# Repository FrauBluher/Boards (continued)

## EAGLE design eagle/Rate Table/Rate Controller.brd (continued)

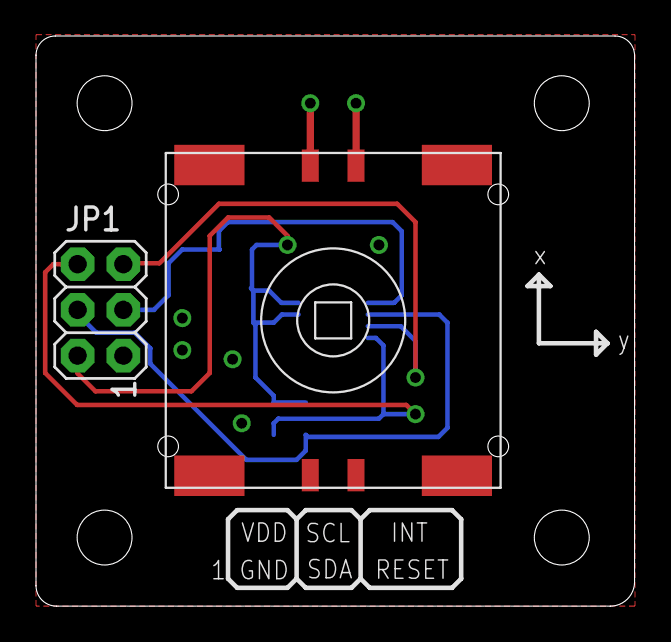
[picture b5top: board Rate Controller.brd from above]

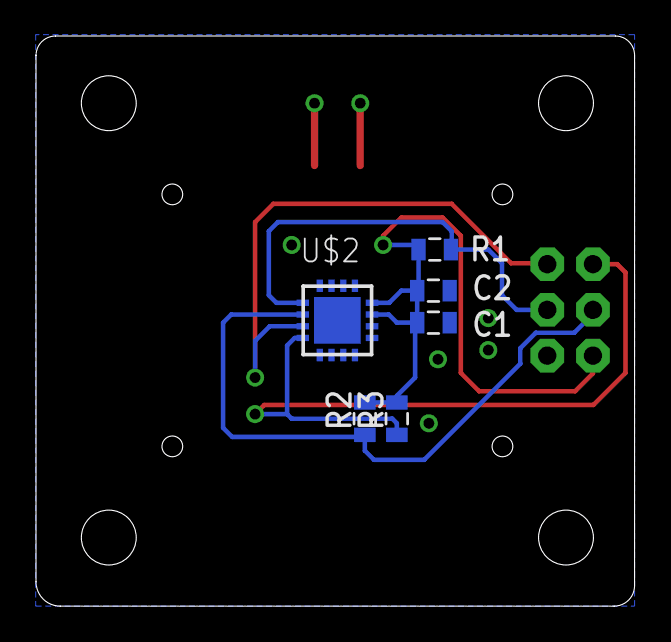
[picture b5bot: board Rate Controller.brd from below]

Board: 2 copper layers, 33.3 x 31.7 mm, 12 parts (6 on the bottom side), 6 nets.

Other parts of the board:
E$1, E$2, E$3, E$4: STAND-OFF-TIGHT

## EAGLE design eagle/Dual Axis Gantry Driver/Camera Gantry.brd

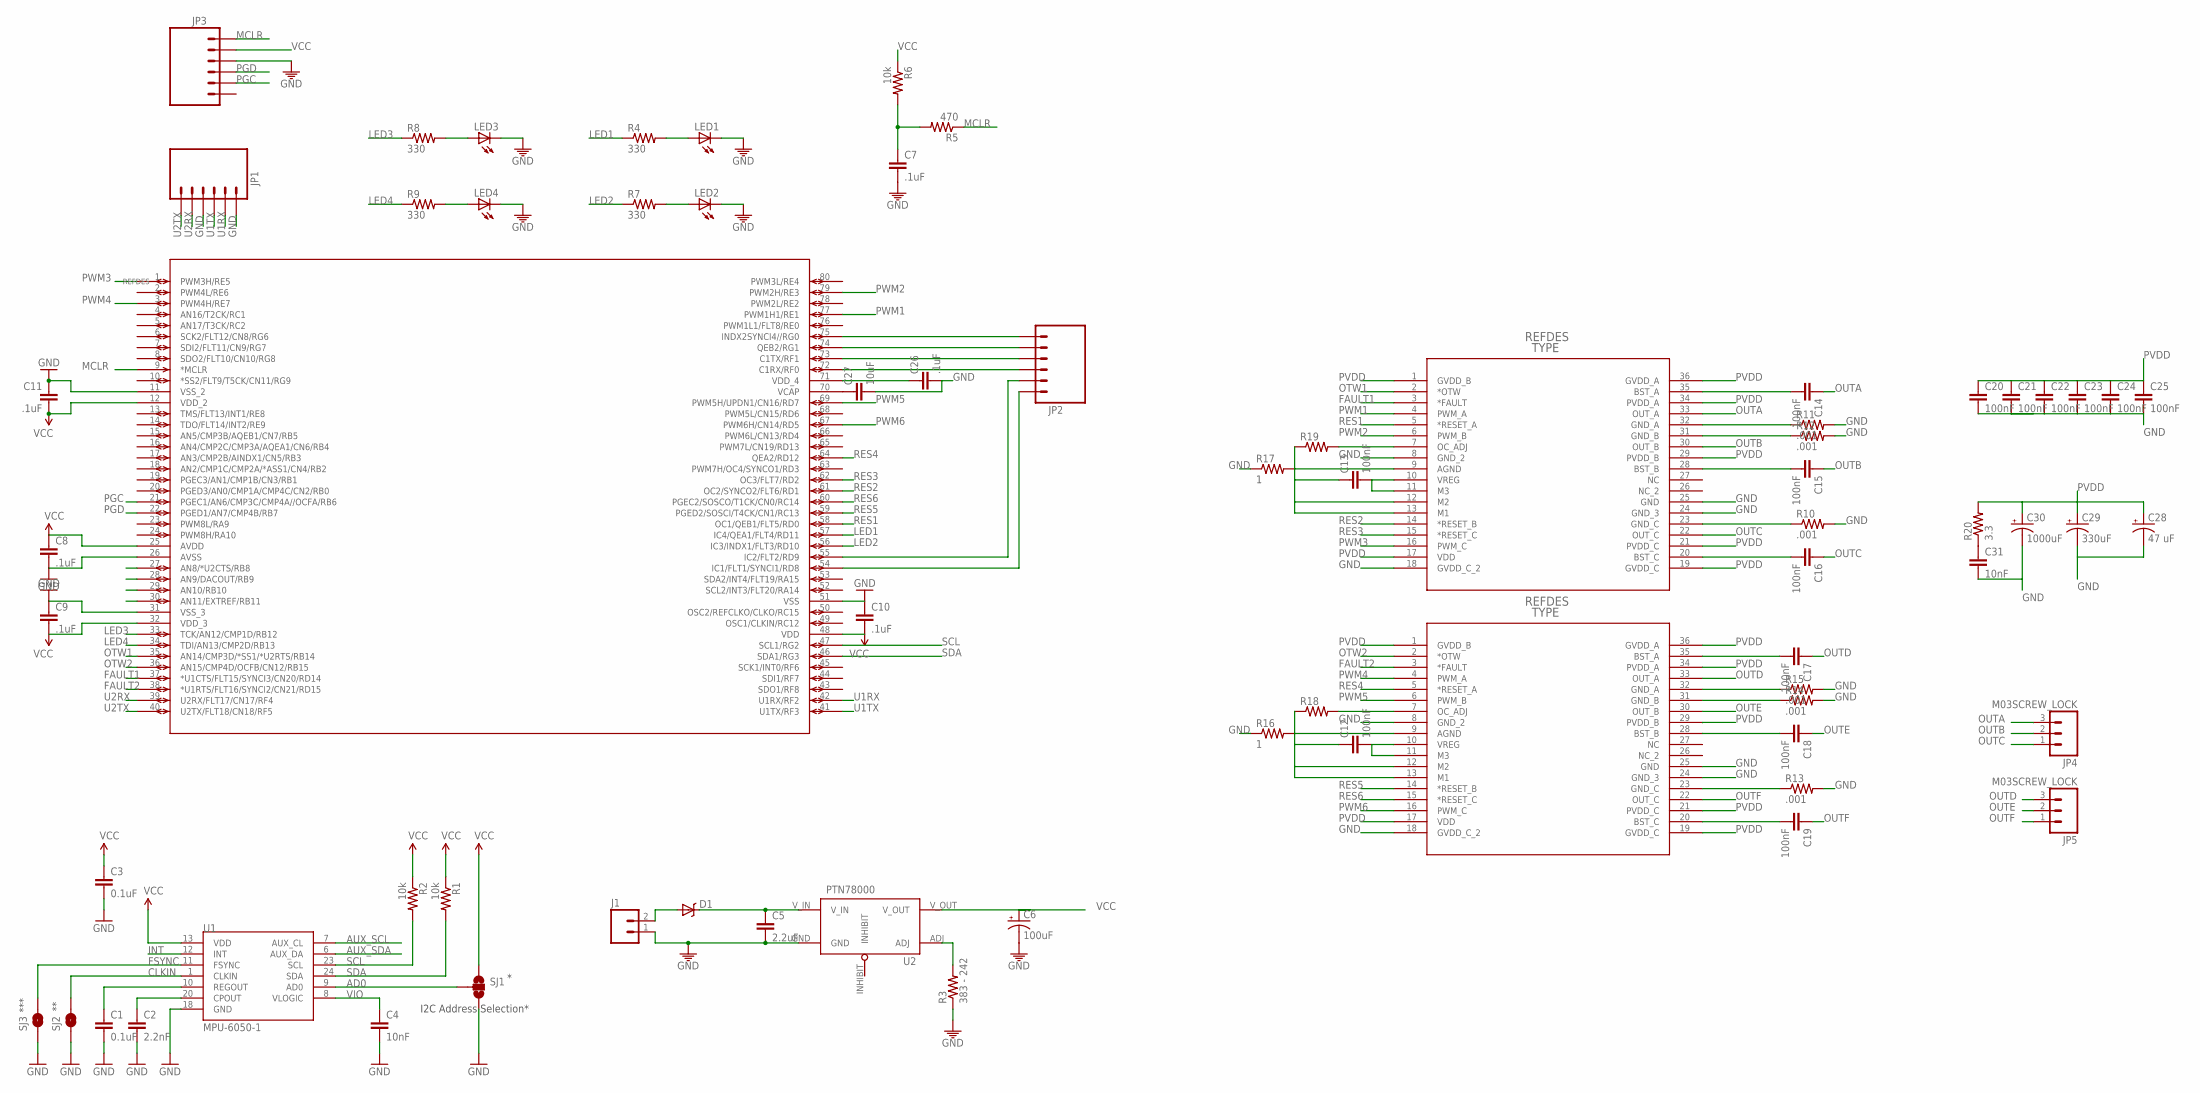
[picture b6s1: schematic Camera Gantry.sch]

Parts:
C1, C3: 0.1uF; 1206
C2: 2.2nF; 1206
C4, C31: 10nF; 1206
C5: 2.2uF; 1206
C6: 100uF; CPOL-RADIAL-100UF-25V
C7, C8, C9, C10, C11, C26: .1uF; 1206
C12, C13, C14, C15, C16, C17, C18, C19, C20, C21, C22, C23, C24, C25: 100nF; 1206
C27: 10uF; 1206
C28: 47 uF; CPOL-RADIAL-10UF-25V
C29: 330uF; CPOL-RADIAL-100UF-25V
C30: 1000uF; CPOL-RADIAL-1000UF-25V
D1: DIODE-SCHOTTKY240A; SMA-DIODE-B240A
J1: M025MM; SCREWTERMINAL-5MM-2
JP1, JP2: M06SIP; 1X06
JP3: M06LOCK; 1X06_LOCK
JP4, JP5: M03SCREW_LOCK; SCREWTERMINAL-3.5MM-3_LOCK.007S
LED1, LED2, LED3, LED4: LED1206; LED-1206
R1, R2, R6: 10k; 0805
R3: 383 - 242; 0805
R4, R7, R8, R9: 330; 0805
R5: 470; 0805
R10, R11, R12, R13, R14, R15: .001; R2512
R16, R17: 1; 0805
R18, R19: RESISTOR0805-RES; 0805
R20: 3.3; 0805
SJ1: SOLDERJUMPER_2WAYPASTE2&3; SJ_3_PASTE2&3
SJ2, SJ3: SOLDERJUMPERTRACE; SJ_2S-TRACE
U1: MPU-6050-1; QFN-24-4MM2
U2: PTN78000
U3, U4: DRV8332_DKD_36; DKD36
U$1: DSPIC33FJ64GS608; TQFP80_12X12MC

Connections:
AD0: SJ1.2, U1.9 (AD0)
AUX_SCL: U1.7 (AUX_CL)
AUX_SDA: U1.6 (AUX_DA)
CLKIN: SJ2.2, U1.1 (CLKIN)
FAULT1: U3.3 (*FAULT), U$1.37 (*U1CTS/FLT15/SYNCI3/CN20/RD14)
FAULT2: U4.3 (*FAULT), U$1.38 (*U1RTS/FLT16/SYNCI2/CN21/RD15)
FSYNC: SJ3.2, U1.11 (FSYNC)
GND: C1.2, C2.2, C3.2, C4.2, C5.2, C6.2 (-), C7.2, C8.2, C9.1, C10.1, C11.1, C20.2, C21.2, C22.2, C23.2, C24.2, C25.2, C26.2, C27.2, C28.2 (-), C29.2 (-), C30.2 (-), C31.2, J1.1, JP1.1, JP1.4, JP3.3, LED1.C, LED2.C, LED3.C, LED4.C, R3.1, R10.2, R11.2, R12.2, R13.2, R14.2, R15.2, R16.1, R17.1, SJ1.3, SJ2.1, SJ3.1, U1.18 (GND), U2.GND, U3.8 (GND_2), U3.18 (GVDD_C_2), U3.24 (GND_3), U3.25 (GND), U4.8 (GND_2), U4.18 (GVDD_C_2), U4.24 (GND_3), U4.25 (GND), U$1.11 (VSS_2), U$1.26 (AVSS), U$1.31 (VSS_3), U$1.51 (VSS)
INT: U1.12 (INT)
LED1: R4.1, U$1.57 (IC4/QEA1/FLT4/RD11)
LED2: R7.1, U$1.56 (IC3/INDX1/FLT3/RD10)
LED3: R8.1, U$1.33 (TCK/AN12/CMP1D/RB12)
LED4: R9.1, U$1.34 (TDI/AN13/CMP2D/RB13)
MCLR: JP3.1, R5.1, U$1.9 (*MCLR)
unnamed: LED1.A, R4.2
unnamed: C7.1, R5.2, R6.2
unnamed: C2.1, U1.20 (CPOUT)
unnamed: LED2.A, R7.2
unnamed: C1.1, U1.10 (REGOUT)
unnamed: R3.2, U2.ADJ
unnamed: D1.A, J1.2
unnamed: LED3.A, R8.2
unnamed: LED4.A, R9.2
unnamed: R11.1, U3.32 (GND_A)
unnamed: R12.1, U3.31 (GND_B)
unnamed: R10.1, U3.23 (GND_C)
unnamed: C13.1, R17.2, R19.1, U3.9 (AGND), U3.12 (M2), U3.13 (M1)
unnamed: C12.1, R16.2, R18.1, U4.9 (AGND), U4.12 (M2), U4.13 (M1)
unnamed: R18.2, U4.7 (OC_ADJ)
unnamed: C12.2, U4.10 (VREG), U4.11 (M3)
unnamed: C13.2, U3.10 (VREG), U3.11 (M3)
unnamed: R15.1, U4.32 (GND_A)
unnamed: R14.1, U4.31 (GND_B)
unnamed: R13.1, U4.23 (GND_C)
unnamed: C17.2, U4.35 (BST_A)
unnamed: C18.2, U4.28 (BST_B)
unnamed: C19.2, U4.20 (BST_C)
unnamed: C14.2, U3.35 (BST_A)
unnamed: C15.2, U3.28 (BST_B)
unnamed: C16.2, U3.20 (BST_C)
unnamed: JP2.3, U$1.72 (C1RX/RF0)
unnamed: JP2.4, U$1.73 (C1TX/RF1)
unnamed: JP2.5, U$1.74 (QEB2/RG1)
unnamed: R19.2, U3.7 (OC_ADJ)
unnamed: JP2.6, U$1.75 (INDX2SYNCI4//RG0)
unnamed: JP2.1, U$1.54 (IC1/FLT1/SYNCI1/RD8)
unnamed: JP2.2, U$1.55 (IC2/FLT2/RD9)
unnamed: C26.1, U$1.71 (VDD_4)
unnamed: C27.1, U$1.70 (VCAP)
unnamed: C31.1, R20.1
OTW1: U3.2 (*OTW), U$1.35 (AN14/CMP3D/*SS1/*U2RTS/RB14)
OTW2: U4.2 (*OTW), U$1.36 (AN15/CMP4D/OCFB/CN12/RB15)
OUTA: C14.1, JP4.3, U3.33 (OUT_A)
OUTB: C15.1, JP4.2, U3.30 (OUT_B)
OUTC: C16.1, JP4.1, U3.22 (OUT_C)
OUTD: C17.1, JP5.3, U4.33 (OUT_A)
OUTE: C18.1, JP5.2, U4.30 (OUT_B)
OUTF: C19.1, JP5.1, U4.22 (OUT_C)
PGC: JP3.5, U$1.21 (PGEC1/AN6/CMP3C/CMP4A//OCFA/RB6)
PGD: JP3.4, U$1.22 (PGED1/AN7/CMP4B/RB7)
PVDD: C5.1, C20.1, C21.1, C22.1, C23.1, C24.1, C25.1, C28.1 (+), C29.1 (+), C30.1 (+), D1.C, R20.2, U2.V_IN, U3.1 (GVDD_B), U3.17 (VDD), U3.19 (GVDD_C), U3.21 (PVDD_C), U3.29 (PVDD_B), U3.34 (PVDD_A), U3.36 (GVDD_A), U4.1 (GVDD_B), U4.17 (VDD), U4.19 (GVDD_C), U4.21 (PVDD_C), U4.29 (PVDD_B), U4.34 (PVDD_A), U4.36 (GVDD_A)
PWM1: U3.4 (PWM_A), U$1.77 (PWM1H1/RE1)
PWM2: U3.6 (PWM_B), U$1.79 (PWM2H/RE3)
PWM3: U3.16 (PWM_C), U$1.1 (PWM3H/RE5)
PWM4: U4.4 (PWM_A), U$1.3 (PWM4H/RE7)
PWM5: U4.6 (PWM_B), U$1.69 (PWM5H/UPDN1/CN16/RD7)
PWM6: U4.16 (PWM_C), U$1.67 (PWM6H/CN14/RD5)
RES1: U3.5 (*RESET_A), U$1.58 (OC1/QEB1/FLT5/RD0)
RES2: U3.14 (*RESET_B), U$1.61 (OC2/SYNCO2/FLT6/RD1)
RES3: U3.15 (*RESET_C), U$1.62 (OC3/FLT7/RD2)
RES4: U4.5 (*RESET_A), U$1.64 (QEA2/RD12)
RES5: U4.14 (*RESET_B), U$1.59 (PGED2/SOSCI/T4CK/CN1/RC13)
RES6: U4.15 (*RESET_C), U$1.60 (PGEC2/SOSCO/T1CK/CN0/RC14)
SCL: R2.2, U1.23 (SCL), U$1.47 (SCL1/RG2)
SDA: R1.2, U1.24 (SDA), U$1.46 (SDA1/RG3)
U1RX: JP1.2, U$1.42 (U1RX/RF2)
U1TX: JP1.3, U$1.41 (U1TX/RF3)
U2RX: JP1.5, U$1.39 (U2RX/FLT17/CN17/RF4)
U2TX: JP1.6, U$1.40 (U2TX/FLT18/CN18/RF5)
VCC: C3.1, C6.1 (+), C8.1, C9.2, C10.2, C11.2, JP3.2, R1.1, R2.1, R6.1, SJ1.1, U1.13 (VDD), U2.V_OUT, U$1.12 (VDD_2), U$1.25 (AVDD), U$1.32 (VDD_3), U$1.48 (VDD)
VIO: C4.1, U1.8 (VLOGIC)

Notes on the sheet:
I2C Address Selection*
***

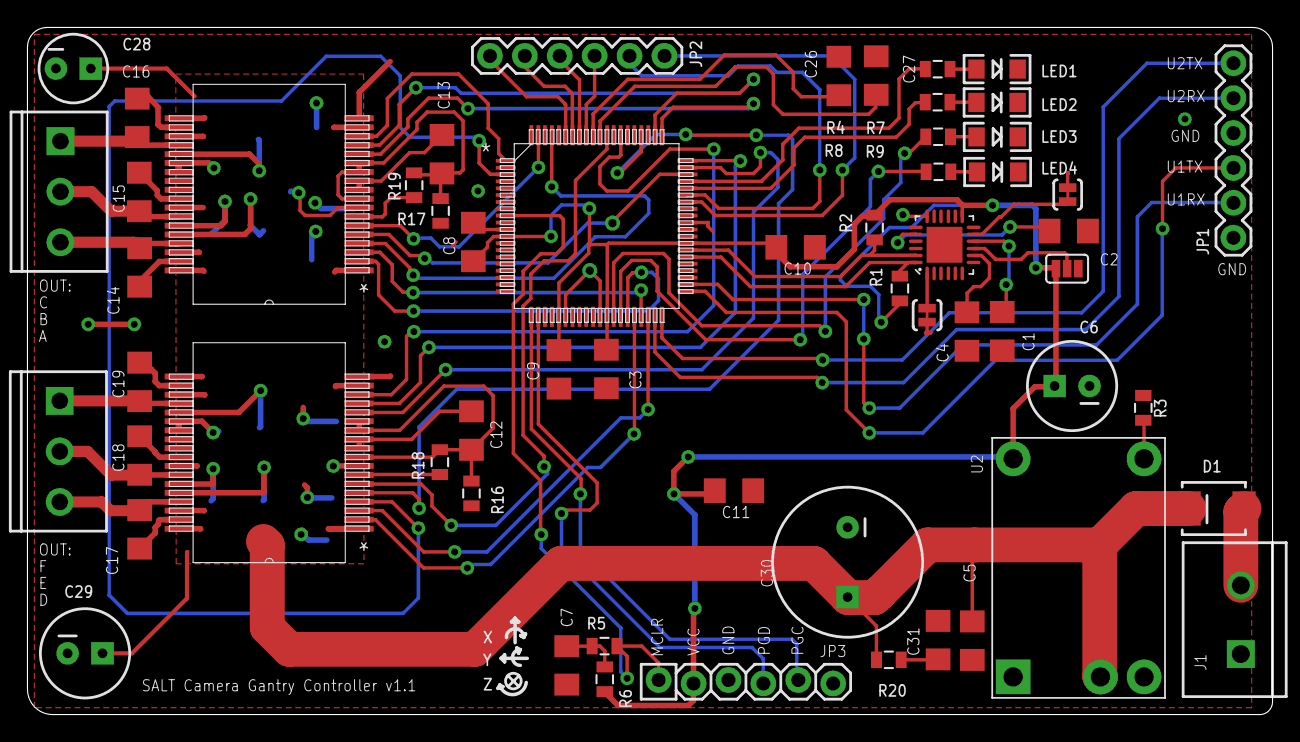
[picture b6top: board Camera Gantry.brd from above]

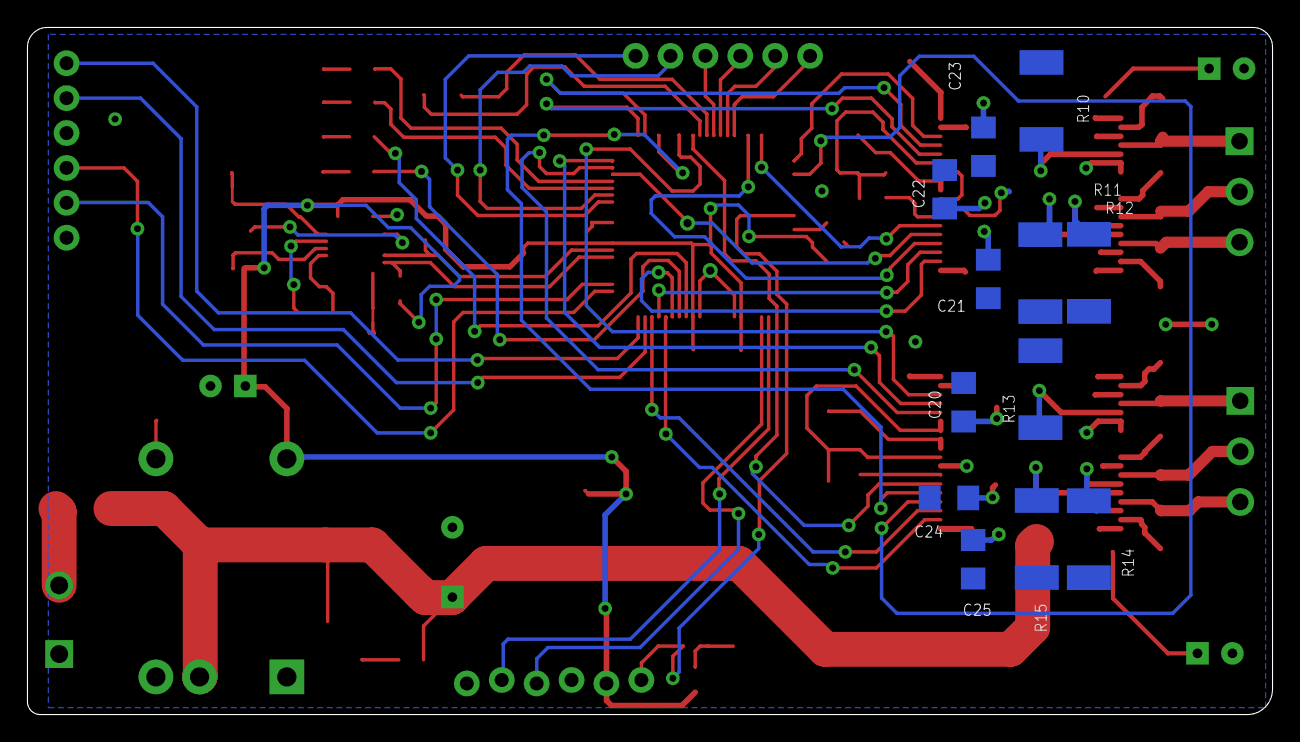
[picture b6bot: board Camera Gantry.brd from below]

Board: 2 copper layers, 90.6 x 50.0 mm, 70 parts (12 on the bottom side), 78 nets.

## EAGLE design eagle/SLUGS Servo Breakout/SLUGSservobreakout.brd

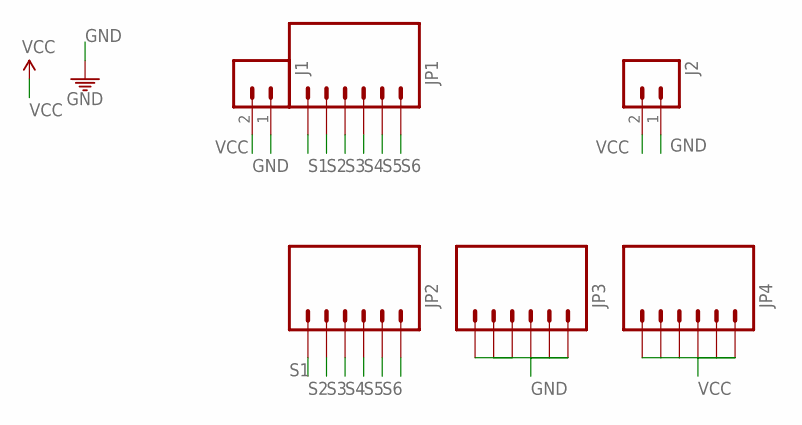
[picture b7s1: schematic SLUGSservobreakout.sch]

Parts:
J1, J2: M02PTH; 1X02
JP1, JP2, JP3, JP4: M06SIP; 1X06

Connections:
GND: J1.1 (2), J2.1 (2), JP3.1, JP3.2, JP3.3, JP3.4, JP3.5, JP3.6
S1: JP1.6, JP2.6
S2: JP1.5, JP2.5
S3: JP1.4, JP2.4
S4: JP1.3, JP2.3
S5: JP1.2, JP2.2
S6: JP1.1, JP2.1
VCC: J1.2 (1), J2.2 (1), JP4.1, JP4.2, JP4.3, JP4.4, JP4.5, JP4.6

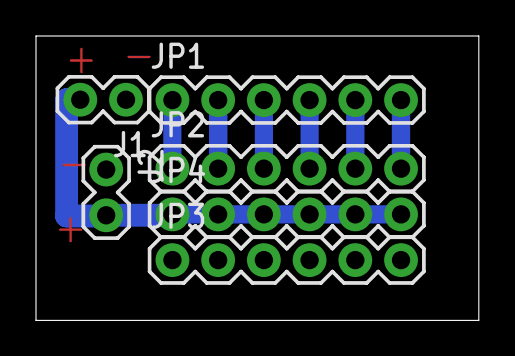
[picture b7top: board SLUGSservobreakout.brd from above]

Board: 2 copper layers, 24.6 x 15.8 mm, 6 parts (0 on the bottom side), 8 nets.

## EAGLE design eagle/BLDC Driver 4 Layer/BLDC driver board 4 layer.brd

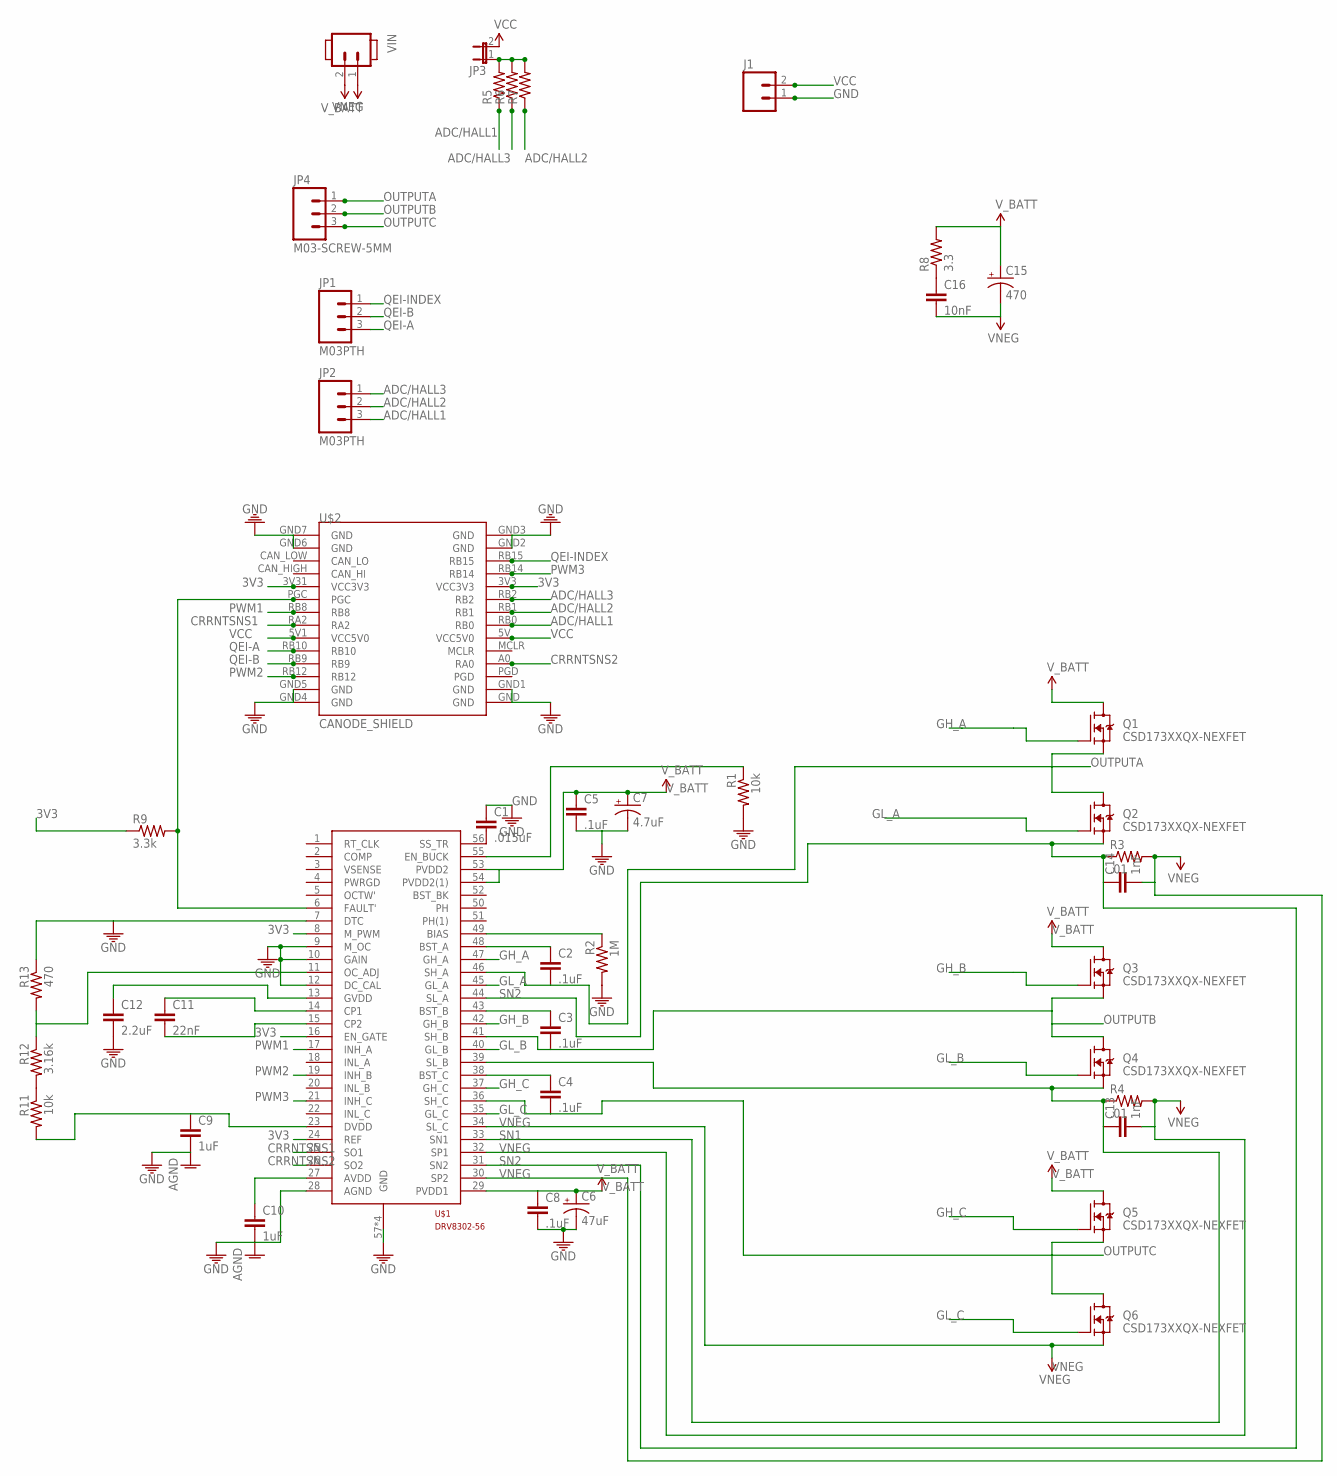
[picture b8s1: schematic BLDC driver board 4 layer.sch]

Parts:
C1: .015uF; 1206
C2, C3, C4, C5, C8: .1uF; 1206
C6: 47uF; CPOL-RADIAL-6.3MM
C7: 4.7uF; CPOL-RADIA-5MM
C9, C10: 1uF; 1206
C11: 22nF; 1206
C12: 2.2uF; 1206
C13, C14: 1nF; 1206
C15: 470; CPOL-RADIAL-1000UF-63V
C16: 10nF; 1206
J1: M02; SOCKET-MALE-2.54MM-2
JP1, JP2: M03PTH; 1X03
JP3: JP1E; JP1
JP4: M03-SCREW-5MM; SCREWTERMINAL-5MM-3
Q1, Q2, Q3, Q4, Q5, Q6: CSD173XXQX-NEXFET; CSD173XXQX
R1, R11: 10k; 0805
R2: 1M; 0805
R3, R4: .01; SMT-REF
R5, R6, R7: RESISTOR0805-RES; 0805
R8: 3.3; 1206
R9: 3.3k; 0805
R12: 3.16k; 0805
R13: 470; 0805
U$1: DRV8302-56; HTSSOP56
U$2: CANODE_SHIELD
VIN: SCREWTERM02; SCREW_TERMINAL-5.08MM-2

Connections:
3V3: R9.1, U$1.8 (M_PWM), U$1.16 (EN_GATE), U$1.24 (REF), U$2.3V3 (VCC3V3), U$2.3V31 (VCC3V3)
ADC/HALL1: JP2.3, R6.1, U$2.RB0
ADC/HALL2: JP2.2, R7.1, U$2.RB1
ADC/HALL3: JP2.1, R5.1, U$2.RB2
CRRNTSNS1: U$1.25 (SO1), U$2.RA2
CRRNTSNS2: U$1.26 (SO2), U$2.A0 (RA0)
GH_A: Q1.G, U$1.47 (GH_A)
GH_B: Q3.G, U$1.42 (GH_B)
GH_C: Q5.G, U$1.37 (GH_C)
GL_A: Q2.G, U$1.45 (GL_A)
GL_B: Q4.G, U$1.40 (GL_B)
GL_C: Q6.G, U$1.35 (GL_C)
GND: C1.1, C5.2, C6.2 (-), C7.2 (-), C8.2, C9.2, C10.2, C12.2, J1.1, R1.2, R2.2, R13.1, U$1.7 (DTC), U$1.9 (M_OC), U$1.10 (GAIN), U$1.12 (DC_CAL), U$1.28 (AGND), U$1.57 (GND), U$1.P$1 (GND), U$1.P$2 (GND), U$1.P$3 (GND), U$2.GND, U$2.GND1 (GND), U$2.GND2 (GND), U$2.GND3 (GND), U$2.GND4 (GND), U$2.GND5 (GND), U$2.GND6 (GND), U$2.GND7 (GND)
unnamed: C1.2, U$1.56 (SS_TR)
unnamed: R9.2, U$1.6 (FAULT'), U$2.PGC
unnamed: R2.1, U$1.49 (BIAS)
unnamed: C2.1, U$1.48 (BST_A)
unnamed: C3.1, U$1.43 (BST_B)
unnamed: C16.1, R8.1
unnamed: C4.1, U$1.38 (BST_C)
unnamed: R11.1, R12.2
unnamed: R1.1, U$1.55 (EN_BUCK)
unnamed: R12.1, R13.2, U$1.11 (OC_ADJ)
unnamed: JP3.1, R5.2, R6.2, R7.2
unnamed: C10.1, U$1.27 (AVDD)
unnamed: C9.1, R11.2, U$1.23 (DVDD)
unnamed: C11.1, U$1.14 (CP1)
unnamed: C11.2, U$1.15 (CP2)
unnamed: C12.1, U$1.13 (GVDD)
OUTPUTA: C2.2, JP4.1, Q1.S1 (S), Q1.S2 (S), Q1.S3 (S), Q2.D, Q2.P$1 (D), Q2.P$2 (D), Q2.P$3 (D), Q2.P$4 (D), Q2.P$5 (D), Q2.P$6 (D), Q2.P$7 (D), Q2.P$8 (D), Q2.P$9 (D), U$1.46 (SH_A)
OUTPUTB: C3.2, JP4.2, Q3.S1 (S), Q3.S2 (S), Q3.S3 (S), Q4.D, Q4.P$1 (D), Q4.P$2 (D), Q4.P$3 (D), Q4.P$4 (D), Q4.P$5 (D), Q4.P$6 (D), Q4.P$7 (D), Q4.P$8 (D), Q4.P$9 (D), U$1.41 (SH_B)
OUTPUTC: C4.2, JP4.3, Q5.S1 (S), Q5.S2 (S), Q5.S3 (S), Q6.D, Q6.P$1 (D), Q6.P$2 (D), Q6.P$3 (D), Q6.P$4 (D), Q6.P$5 (D), Q6.P$6 (D), Q6.P$7 (D), Q6.P$8 (D), Q6.P$9 (D), U$1.36 (SH_C)
PWM1: U$1.17 (INH_A), U$2.RB8
PWM2: U$1.19 (INH_B), U$2.RB12
PWM3: U$1.21 (INH_C), U$2.RB14
QEI-A: JP1.3, U$2.RB10
QEI-B: JP1.2, U$2.RB9
QEI-INDEX: JP1.1, U$2.RB15
SN1: C13.1, Q4.S1 (S), Q4.S2 (S), Q4.S3 (S), R4.1, R4.P$7 (1), R4.P$8 (1), R4.P$9 (1), R4.P$10 (1), R4.P$11 (1), R4.P$12 (1), U$1.33 (SN1), U$1.39 (SL_B)
SN2: C14.1, Q2.S1 (S), Q2.S2 (S), Q2.S3 (S), R3.1, R3.P$7 (1), R3.P$8 (1), R3.P$9 (1), R3.P$10 (1), R3.P$11 (1), R3.P$12 (1), U$1.31 (SN2), U$1.44 (SL_A)
VCC: J1.2, JP3.2, U$2.5V (VCC5V0), U$2.5V1 (VCC5V0)
VNEG: C13.2, C14.2, C15.2 (-), C16.2, Q6.S1 (S), Q6.S2 (S), Q6.S3 (S), R3.2, R3.P$1 (2), R3.P$2 (2), R3.P$3 (2), R3.P$4 (2), R3.P$5 (2), R3.P$6 (2), R4.2, R4.P$1 (2), R4.P$2 (2), R4.P$3 (2), R4.P$4 (2), R4.P$5 (2), R4.P$6 (2), U$1.30 (SP2), U$1.32 (SP1), U$1.34 (SL_C), VIN.2
V_BATT: C5.1, C6.1 (+), C7.1 (+), C8.1, C15.1 (+), Q1.D, Q1.P$1 (D), Q1.P$2 (D), Q1.P$3 (D), Q1.P$4 (D), Q1.P$5 (D), Q1.P$6 (D), Q1.P$7 (D), Q1.P$8 (D), Q1.P$9 (D), Q3.D, Q3.P$1 (D), Q3.P$2 (D), Q3.P$3 (D), Q3.P$4 (D), Q3.P$5 (D), Q3.P$6 (D), Q3.P$7 (D), Q3.P$8 (D), Q3.P$9 (D), Q5.D, Q5.P$1 (D), Q5.P$2 (D), Q5.P$3 (D), Q5.P$4 (D), Q5.P$5 (D), Q5.P$6 (D), Q5.P$7 (D), Q5.P$8 (D), Q5.P$9 (D), R8.2, U$1.29 (PVDD1), U$1.53 (PVDD2), U$1.54 (PVDD2(1)), VIN.1

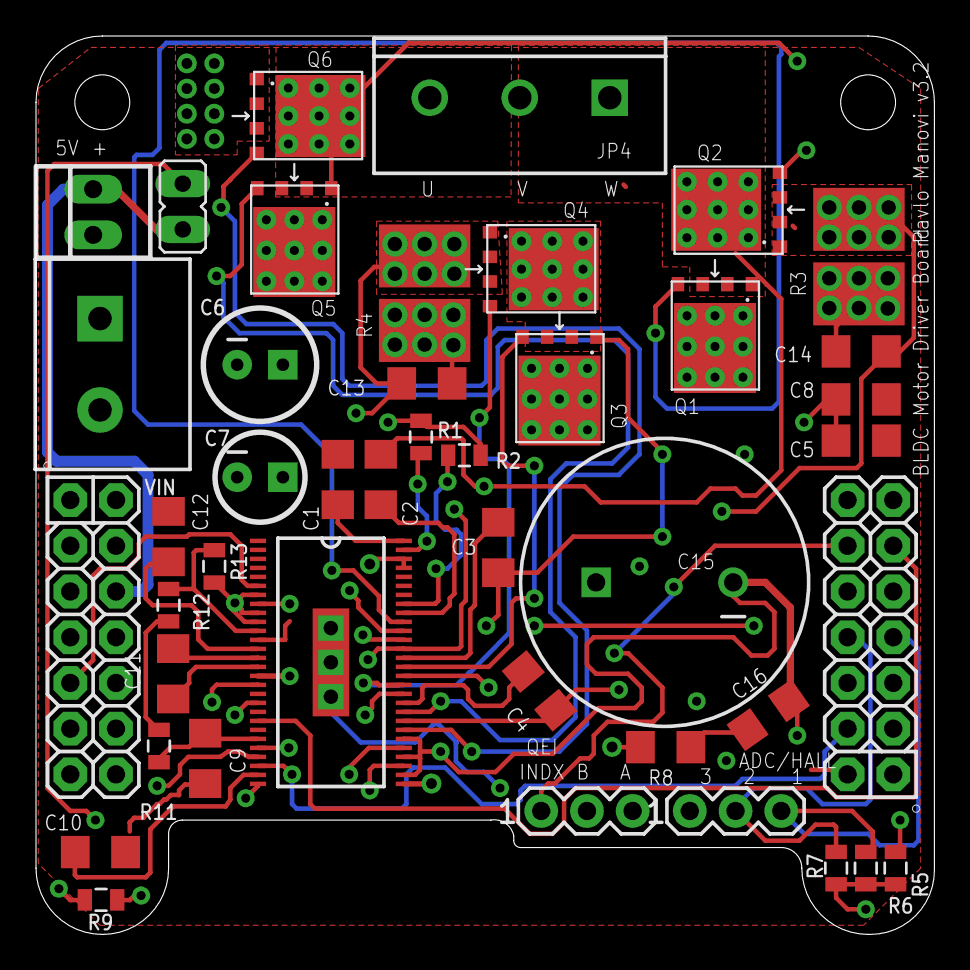
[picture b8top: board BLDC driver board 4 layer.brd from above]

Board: 4 copper layers, 49.9 x 49.9 mm, 44 parts (0 on the bottom side), 43 nets.

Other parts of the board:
E$1, E$2: STAND-OFF-TIGHT

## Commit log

2012-11-04 Initial commit.
2012-11-08 Started working on new driver board.
2012-11-17 Finished BLDC Driver v2.1
2013-01-10 Finished v 2 of the BLDC driver board
    Finished the alumni board
    Finished the MAC.PHY_shield for the ASL CAN node.
2013-01-10 Added gerber files for surface mount version of the MAC.PHY_shield
2013-01-16 Finished the PDIP dev board for the enc28J60
2013-01-21 Added my ASL.lbr
2013-02-02 Changed ENC board
2013-02-04 Added Alumni Boards and new version of MAC.PHY shield
2013-03-05 Updated Zigbee adapter
2013-03-25 Started Hula Proto Board.
2013-03-30 Create Ari
2013-04-02 Added BLDC 4 Layer Board For CAN node v3
2013-04-02 More changes to the 4-Layer BLDC Board.
2013-04-03 More changes to bldc 4-layer, cleaned up files.
2013-04-03 Changed spacing on pin headers.
2013-04-03 4-layer bldc work, finding more space.
2013-04-04 Changes to bldc 4-layer. Finished ethershield v3.
2013-04-04 Removed ASL.lbr as it is in the ASL_eCAD repo.
2013-04-04 Removed dependencies from ASL.lbr in /Boards.
2013-04-04 Updated some footprints.
2013-04-06 exploded 4-layer bldc due to space boon
2013-04-09 added .lbr files used
2013-04-09 fixed library links
2013-04-09 More BLDC work. Updated ASL.lbr.
2013-04-10 Completed BLDC 4-layer and new Ether-shield
2013-04-12 Polishing up 4-layer BLDC
2013-04-12 Polished up MAC-PHY Board.
2013-04-12 Ready for Board Run.
2013-04-15 Sent out boards to itead, last minute changes included.
2013-04-18 New rs232 adapter for xbee.
2013-05-20 New 1-Axis Test BLDC breakout for gluon stab
2013-05-21 Finished 1-Axis Dev for Camera Stab.
2013-05-22 Added some filtering to the 1-Axis Gantry Board
2013-06-04 Dual Axis SALT Board v1.1 Completed
2013-10-02 Updating libraries and DRV83x2 related boards.
2013-10-03 More motor driver refactoring.
2013-10-04 More work on the new driver boards.
2014-05-07 Did some clean-up to the directory, added an ams EasyPoint breakout board and consolidated PMSMmini board as well as pavlo.lbr.
2014-05-18 Added RGB 8x8 Matrix Driver Board
2014-05-18 Finished gerbers.
2014-05-26 More 121 Work
2014-07-09 Added Nanopore current amplifier circuit work.
2014-07-23 Current amp work.
2014-11-03 Fixed current amp board.
